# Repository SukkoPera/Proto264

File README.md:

# Proto264
Proto264 is an Open Hardware prototyping board for the Expansion port of the Commodore 16, 114 and Plus/4 computers

## Summary
**This board does NOTHING out-of-the box**, it's meant to be the first brick upon which you can prototype your own Expansion port-based designs.

It's basically a matrix of 2.54mm-spaced soldering points with easy access to all the signals available on the port and plenty of power points. With a few wires you can easily build anything you have in mind.

You can also solder a 2.54mm pin header so that you can easily connect Dupont headers, scope/logic analyzer probes, etc.

The TOP side is clearly indicated in order to avoid plugging it upside-down, please pay attention to that!

If you think you need more solder points, keep in mind that this board was sized just under 10x10cm in order to allow it to be produced cheaply (you can get 10 for $5 from PCBWay, see [below](#support-the-project)).

## Releases
If you want to get this board produced, you are recommended to get [the latest release](https://github.com/SukkoPera/Proto264/releases) rather than the current git version, as the latter might be under development and is not guaranteed to be working.

Every release is accompanied by its Bill Of Materials (BOM) file and any relevant notes about it, which you are recommended to read carefully.

## License
The Proto264 documentation, including the design itself, is copyright &copy; SukkoPera 2023 and is licensed under the [Creative Commons Attribution-NonCommercial-ShareAlike 4.0 International License](https://creativecommons.org/licenses/by-nc-sa/4.0/).

This documentation is distributed *as is* and WITHOUT ANY EXPRESS OR IMPLIED WARRANTIES whatsoever with respect to its functionality, operability or use, including, without limitation, any implied warranties OF MERCHANTABILITY, SATISFACTORY QUALITY, FITNESS FOR A PARTICULAR PURPOSE or infringement. We expressly disclaim any liability whatsoever for any direct, indirect, consequential, incidental or special damages, including, without limitation, lost revenues, lost profits, losses resulting from business interruption or loss of data, regardless of the form of action or legal theory under which the liability may be asserted, even if advised of the possibility or likelihood of such damages.

## Support the Project
If you want to get some boards manufactured, you can get them from PCBWay through this link:

You get my gratitude and cheap, professionally-made and good quality PCBs, I get some credit that will help with this and [other projects](https://www.pcbway.com/project/member/shareproject/?bmbid=41100). You won't even have to worry about the various PCB options, it's all pre-configured for you!

Also, if you still have to register, [you can use this link](https://www.pcbway.com/setinvite.aspx?inviteid=41100) to get some bonus initial credit (and yield me some more).

You can also buy me a coffee if you want:

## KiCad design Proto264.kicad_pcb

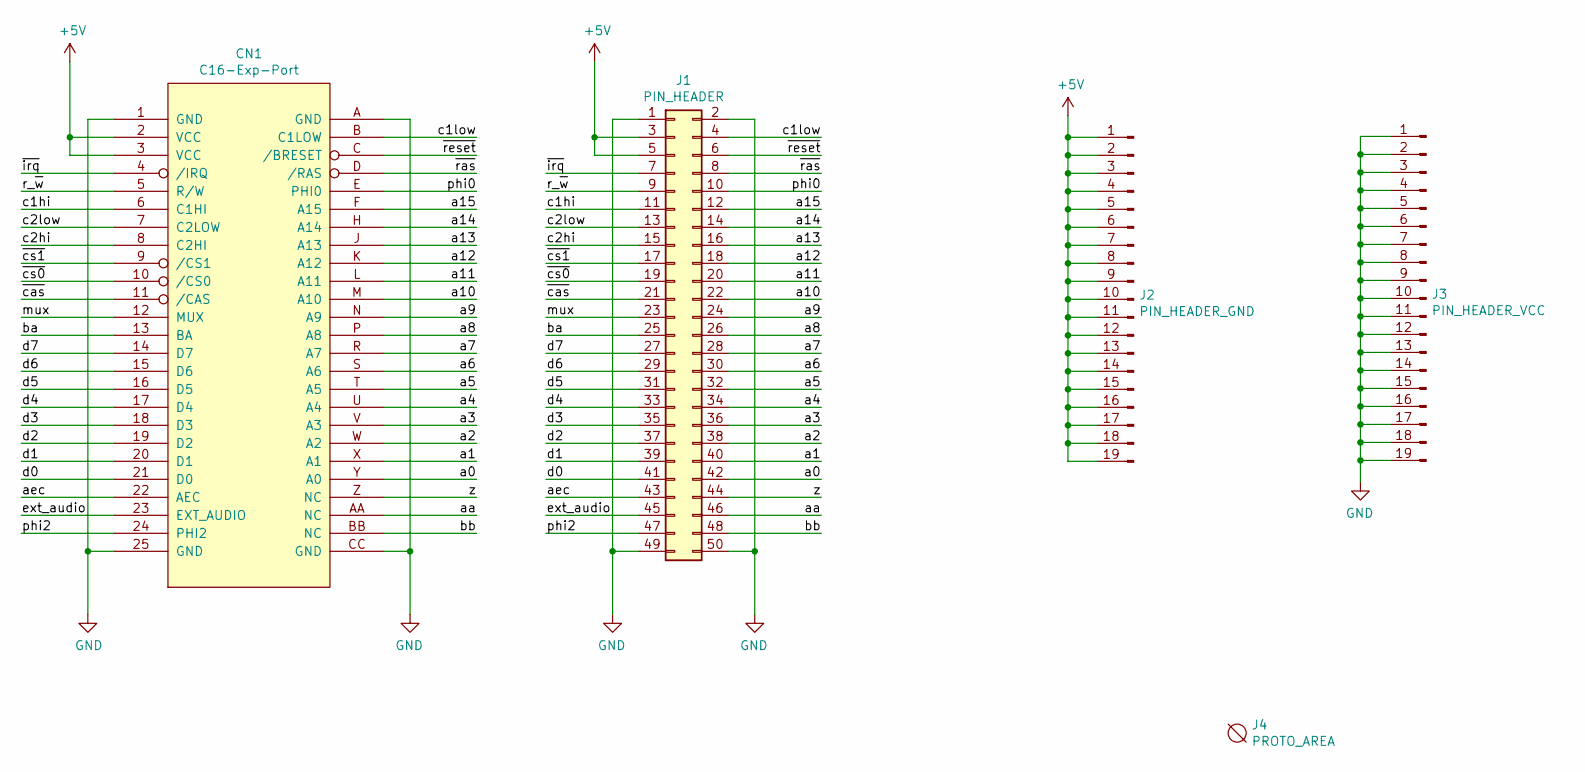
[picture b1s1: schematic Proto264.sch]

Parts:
CN1: C16-Exp-Port; C16_Cart_Conn
J1: PIN_HEADER; PinHeader_2x25_P2.54mm_Vertical
J2: PIN_HEADER_GND; PinHeader_1x19_P2.54mm_Vertical
J3: PIN_HEADER_VCC; PinHeader_1x19_P2.54mm_Vertical
J4: PROTO_AREA; ProtoArea35x19

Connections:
+5V: CN1.2 (VCC), CN1.3 (VCC), J1.3, J1.5, J2.1, J2.2, J2.3, J2.4, J2.5, J2.6, J2.7, J2.8, J2.9, J2.10, J2.11, J2.12, J2.13, J2.14, J2.15, J2.16, J2.17, J2.18, J2.19
/a0: CN1.Y (A0), J1.42
/a1: CN1.X (A1), J1.40
/a2: CN1.W (A2), J1.38
/a3: CN1.V (A3), J1.36
/a4: CN1.U (A4), J1.34
/a5: CN1.T (A5), J1.32
/a6: CN1.S (A6), J1.30
/a7: CN1.R (A7), J1.28
/a8: CN1.P (A8), J1.26
/a9: CN1.N (A9), J1.24
/a10: CN1.M (A10), J1.22
/a11: CN1.L (A11), J1.20
/a12: CN1.K (A12), J1.18
/a13: CN1.J (A13), J1.16
/a14: CN1.H (A14), J1.14
/a15: CN1.F (A15), J1.12
/aa: CN1.AA (NC), J1.46
/aec: CN1.22 (AEC), J1.43
/ba: CN1.13 (BA), J1.25
/bb: CN1.BB (NC), J1.48
/c1hi: CN1.6 (C1HI), J1.11
/c1low: CN1.B (C1LOW), J1.4
/c2hi: CN1.8 (C2HI), J1.15
/c2low: CN1.7 (C2LOW), J1.13
/d0: CN1.21 (D0), J1.41
/d1: CN1.20 (D1), J1.39
/d2: CN1.19 (D2), J1.37
/d3: CN1.18 (D3), J1.35
/d4: CN1.17 (D4), J1.33
/d5: CN1.16 (D5), J1.31
/d6: CN1.15 (D6), J1.29
/d7: CN1.14 (D7), J1.27
/ext_audio: CN1.23 (EXT_AUDIO), J1.45
/mux: CN1.12 (MUX), J1.23
/phi0: CN1.E (PHI0), J1.10
/phi2: CN1.24 (PHI2), J1.47
/r_~w: CN1.5 (R/W), J1.9
/z: CN1.Z (NC), J1.44
/~cas: CN1.11 (/CAS), J1.21
/~cs0: CN1.10 (/CS0), J1.19
/~cs1: CN1.9 (/CS1), J1.17
/~irq: CN1.4 (/IRQ), J1.7
/~ras: CN1.D (/RAS), J1.8
/~reset: CN1.C (/BRESET), J1.6
GND: CN1.1 (GND), CN1.25 (GND), CN1.A (GND), CN1.CC (GND), J1.1, J1.2, J1.49, J1.50, J3.1, J3.2, J3.3, J3.4, J3.5, J3.6, J3.7, J3.8, J3.9, J3.10, J3.11, J3.12, J3.13, J3.14, J3.15, J3.16, J3.17, J3.18, J3.19

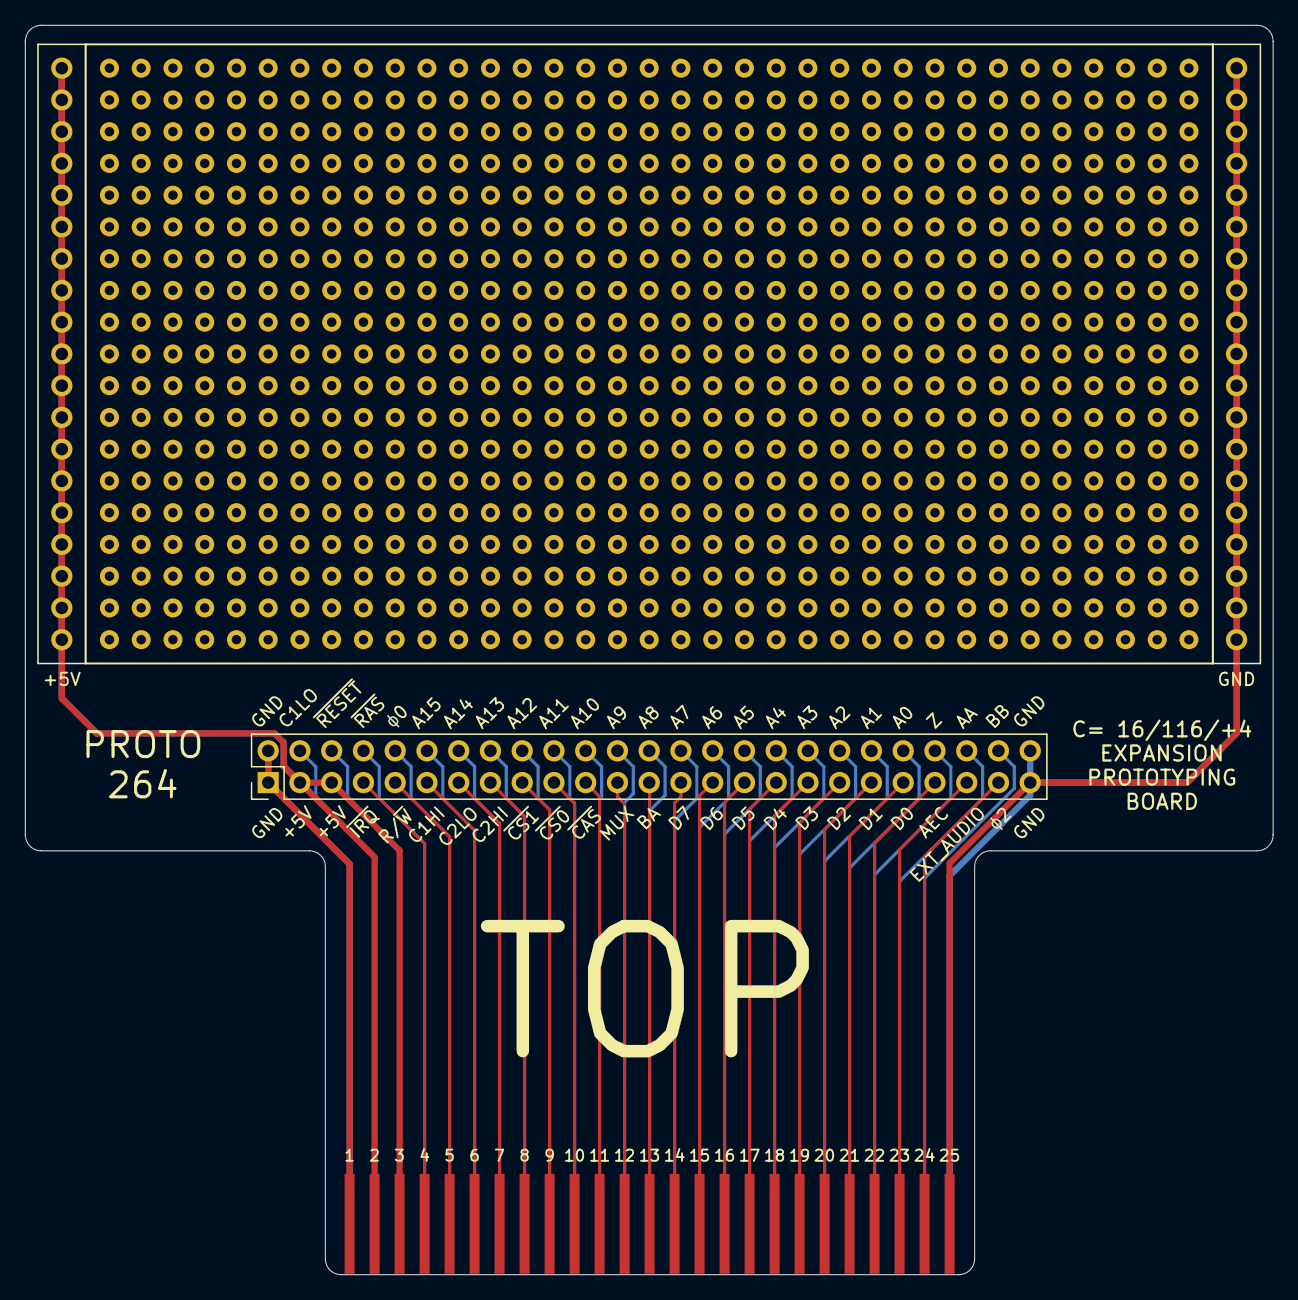
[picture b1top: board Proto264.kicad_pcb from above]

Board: 2 copper layers, 99.8 x 99.9 mm, 5 parts (0 on the bottom side), 46 nets.

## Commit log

2022-07-28 Correct label
2023-04-07 Add renders
2023-04-07 Add board link

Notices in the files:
Proto264.kicad_pcb:
Licensed under CC BY-NC-SA 4.0
